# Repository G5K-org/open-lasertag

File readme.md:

<div align="center">

# Open Lasertag

**Infrarot-Lasertag zum Selberbauen – ESP32-S3 in der Waffe, passive Sensorweste, Spielserver in Python**

</div>

## Was ist das?

Ein komplettes Lasertag-System im Eigenbau für Spiele in einer großen Halle:

- **Waffe:** ein 3D-gedrucktes MP5-Gehäuse mit einer eigenen Platine. Darauf
  sitzt ein ESP32-S3, der alles steuert: IR-Schuss, Trefferauswertung,
  Lebens- und Munitionsanzeige, Mündungsfeuer, Vibration, Sound, Akku und WLAN.
- **Weste:** nur passive IR-Empfänger (TSOP34838) an Stirnband, Brust, Rücken
  und Schultern, per Kabel an der Waffe. Die Weste hat keine eigene Elektronik.
- **Server:** ein Python-Programm mit Live-Anzeige im Browser. Es zählt
  Punkte, führt Runden und gibt den Respawn frei.
- **Gateway (optional):** ein kleiner ESP32 am Server-PC. Über ihn erreichen
  die Waffen den Server per ESP-NOW, wenn das WLAN ausfällt.

Geschossen wird mit einer 940-nm-IR-LED hinter einer Linse, nicht mit einem
echten Laser. Die Spiellogik läuft lokal in der Waffe, damit Treffer sofort
Licht, Ton und Vibration auslösen. Das Netz meldet nur nach.

## Inhalt

- [Funktionen](#funktionen)
- [Systemüberblick](#systemüberblick)
- [Hardware](#hardware)
- [Gehäuse](#gehäuse)
- [Firmware](#firmware)
- [Server und Live-Anzeige](#server-und-live-anzeige)
- [Schnellstart](#schnellstart)
- [Projektstruktur](#projektstruktur)
- [Stand](#stand)
- [Planung im Detail](#planung-im-detail)
  1. [Grundentscheidungen](#1-grundentscheidungen)
  2. [Architektur](#2-architektur)
  3. [Sensorkabel zwischen Weste und Waffe](#3-sensorkabel-zwischen-weste-und-waffe)
  4. [IR-Protokoll und Trefferlogik](#4-ir-protokoll-und-trefferlogik)
  5. [Netzwerk](#5-netzwerk)
  6. [Anzeige und Feedback](#6-anzeige-und-feedback)
  7. [Risiken und Gegenmaßnahmen](#7-risiken-und-gegenmaßnahmen)
  8. [ESP32-Wahl](#8-esp32-wahl)
  9. [Vorgehen](#9-vorgehen)
  10. [Offene Punkte](#10-offene-punkte)

## Funktionen

| | |
|---|---|
| 🔫 **Schuss** | NEC-codiertes IR-Signal (Team + Spieler-ID), 38 kHz, jeder Schuss 2× gesendet; Ziel 30–50 m Reichweite |
| 🎯 **Treffer** | bis zu 6 Sensoren; Treffer zählt erst bei 2 gültigen Frames in 100 ms, danach 500 ms unverwundbar; Kopftreffer geben Bonuspunkte |
| 💡 **Anzeige** | WS2812-Kette an der Waffe: Lebensbalken grün → gelb → rot, Munition, Teamfarbe, Ringlicht als Mündungsfeuer; Anschlüsse für OLED (I²C) und Drehdrück-Geber |
| 📳 **Feedback** | Rückstoß- und Treffervibration, Soundeffekte über I²S-Verstärker, weißer Blitz bei Treffer, rotes Pulsieren als tot |
| 🔋 **Akku** | 1S-LiPo/18650 mit Schutzschaltung auf der Platine, Laden über USB-C, Spannungs- und Ladeanzeige; per USB auch ohne Akku lauffähig |
| 📡 **Netz** | WLAN mit eigenem Roaming zwischen Access Points, UDP mit HMAC-Signatur, Treffer werden bis zur Bestätigung wiederholt |
| 🛟 **ESP-NOW** | Fallback zum Server über ein Gateway, wenn das WLAN ausfällt; Trefferbestätigung direkt an die Waffe des Schützen (Ton + grüner Blitz) |
| 🖥️ **Server** | Runden mit Zeitlimit, Teamwertung, Respawn-Freigabe, Live-Anzeige und Bedienung im Browser, Latenzmessung pro Hallenzone |

## Systemüberblick

```mermaid
flowchart LR
    subgraph Weste["Weste (nur Sensoren)"]
        T1["TSOP 1<br>Stirn vorn"]
        T2["TSOP 2<br>Stirn hinten"]
        T3["TSOP 3<br>Brust"]
        T4["TSOP 4<br>Rücken"]
        T5["TSOP 5<br>Schultern"]
    end
    subgraph Waffe["Waffe (ESP32-S3)"]
        RX["IR-Empfang<br>RMT + GPIO"]
        GAME["Spiellogik<br>HP, Munition, Respawn"]
        TX["IR-LED<br>38 kHz"]
        FX["WS2812, Ringlicht,<br>Vibration, Sound"]
        NET["WLAN / UDP"]
    end
    SRV["Server (Python)<br>Punkte, Runden"]
    GW["Gateway<br>ESP32-C3"]
    WEB["Browser<br>Live-Anzeige"]
    W2["andere Waffe"]

    Weste -->|"Sensorkabel<br>GX16, 7 Adern"| RX
    RX --> GAME
    GAME --> TX
    GAME --> FX
    GAME <--> NET
    NET <-->|"WLAN: UDP + HMAC"| SRV
    NET <-.->|"Fallback: ESP-NOW"| GW
    GW <-->|USB| SRV
    NET -.->|"ESP-NOW: Treffer bestätigt"| W2
    SRV <-->|WebSocket| WEB
    TX -.->|IR-Schuss| G(("Gegner"))
```

## Hardware

Eine Platine für die ganze Waffe: 59,6 × 55 mm, 4 Lagen, nur SMD-Bauteile, von
Hand geroutet und für die Bestückung bei JLCPCB vorbereitet. Alle Peripherie
hängt an Steckern: Akku, IR-LED, Taster, Motoren, Lautsprecher, WS2812, ein Sensor an der Waffe und
das Sensorkabel der Weste. Ein- und ausgeschaltet wird mit dem Taster des Drehgebers (kurz drücken = ein,
2 s = aus; ausgeschaltet fließen ca. 55 µA). Geladen wird über USB-C mit 2 A.

| Oberseite | Unterseite |
|---|---|
|  |  |

**Auf der Platine:** ESP32-S3-WROOM-1 (16 MB Flash, 8 MB PSRAM; optional WROOM-1U mit externer Antenne), USB-C mit
ESD-Schutz zum Flashen und Laden, Lade- und 5-V-IC IP5306 (2 A Laden), Akkuschutz DW01A + FS8205A,
3,3-V-Regler, MOSFETs für IR-LED und Vibrationsmotor, Pegelwandler für
WS2812, I²S-Verstärker MAX98357A, microSD-Slot für Audio-Dateien (optional SPI-NAND-Flash 128 MB),
GX16-Buchse für das Sensorkabel der Weste (TSOP-Leitungen über 100 Ω).

Schaltplan, Layout, Fertigungsdaten und Design-Entscheidungen:
[kicad/waffe_elektronik/](kicad/waffe_elektronik/) · Pinbelegung:
[pinbelegung.md](pinbelegung.md)

## Gehäuse

Als Basis dient das Modell
[MP5 Toygun Cosplay](https://makerworld.com/de/models/427808-mp5-toygun-cosplay)
von **WIZZY** (MakerWorld). Es ist eine rein statische Requisite und wird für
Platine, Akku, Lautsprecher und Optik ausgehöhlt und angepasst. Vorne an der
Mündung sitzt ein WS2812-Ring als Mündungsfeuer.

Die Originaldateien liegen wegen der MakerWorld-Lizenz nicht im Repo; Download und
Ablage beschreibt [gehaeuse/mp5_toygun_stls/](gehaeuse/mp5_toygun_stls/).

Die Platine sitzt im Unterteil zwischen Magazinschacht und Griff; die senkrechte
USB-C-Buchse schließt bündig mit einer Mulde in der linken Seitenwand ab. Im Schalldämpfer sitzen IR-LED und
verstellbare Linse, vorn das Ringlicht; der 18650-Akku steckt im Magazin, das OLED sitzt
angewinkelt vorn oben am Schaft, der Drehgeber unten im Griff, der Abzug löst einen Mikroschalter aus.
Im Handschutz sitzt ein Lautsprecher Ø 40 mit Basskammer, vorn unter dem Korn der TSOP 6. Gehäusehälften
(6 × M3) und die beiden Hälften des vorderen Handschutzes mit Schalldämpfer (5 × M3) sind mit
Einschmelzmuttern verschraubt; die vorderen Hälften umschließen einen Zapfen am hinteren Handschutz
und sind dort mit je 2 × M3 befestigt (ohne Kleber, lösbar). Das Sensorkabel der Weste steckt unten vorn
am Schaft in einer GX16-7-Buchse (Stecker hängt hinter dem Griff leicht schräg nach hinten unten). Links über
dem Griff ist der Sicherungshebel ein beweglicher Nachladehebel (Wippe auf einen verdeckten Taster). Links oben
über dem ESP32-Modul sitzt eine RP-SMA-Buchse für eine externe Knick-Stabantenne (Variante WROOM-1U), die
senkrecht nach oben neben Kimme und Korn steht. Gehäuse, Zwischenring, Handschutz und Schaft sind
mit Stahlstegen und je zwei Zugankern M4 vorn und hinten verspannt, der Zwischenring ist beidseitig
zentriert. Alle Kabelwege sind geprüft:
[gehaeuse/mp5_umbau/](gehaeuse/mp5_umbau/README.md#kabelwege).
Umgebaute und neue Druckteile: [gehaeuse/mp5_umbau/](gehaeuse/mp5_umbau/). Alle Teile samt
Platine zusammengesetzt: [gehaeuse/baugruppe/](gehaeuse/baugruppe/) (GLB/3MF).

| Umgebaute Waffe | Innen (linke Hälfte, Schaft und Magazin ausgeblendet) |
|---|---|
|  |  |

| Schalldämpfer mit Ringlicht und Linsenhülse | OLED am Schaft |
|---|---|
|  |  |

**Externe Antenne:** RP-SMA-Buchse in der linken Seitenwand, innen Pigtail als Schlaufe zum U.FL des WROOM-1U.

| Außen | Innen (linke Hälfte und Antenne ausgeblendet) |
|---|---|
|  |  |

**Explosionszeichnung:** alle Druckteile, die Platine und die Antennenteile, entlang ihrer Montagerichtung auseinandergezogen.

| Von links vorn | Von rechts |
|---|---|
|  |  |

**Schnitt durch den Schalldämpfer:** Linsenhülse (gold) mit Linse Ø 20 im Innengewinde M24 × 1,5,
von vorn verstellbar; dahinter die IR-LED im Sitz (21 mm hinter der Linse), Kabel nach hinten;
vorn die Frontkappe mit Ringlicht, unten der Kabelkanal für das Ringlicht.

**Schnitt durch den Handschutz** (rechte Hälfte): Lautsprecher Ø 40 (rot) strahlt nach hinten in eine
Schallkammer mit Löchern in den Rillen, davor die geschlossene Basskammer (ca. 42 cm³); oben der
Kabelschacht als offene Nut an der Teilungsfläche, darüber das Korn; rechts (blau) der Zapfen des
hinteren Handschutzes, den die vorderen Hälften umschließen.

**Schnitt durch Gehäuse und Schaft:** GX16-7-Buchse für das Sensorkabel der Weste unten vorn am Schaft
(gold, Mutter in einer Sechskanttasche), Stecker 15° nach hinten unten; der Westenschacht läuft schräg nach
vorn in den Motorschacht und zur Platine (J2).

## Firmware

ESP-IDF v6.0, nur offizielle Espressif-Komponenten. WLAN und Netz laufen auf
Core 0, IR-Empfang und Spiellogik auf Core 1.

- **IR:** Senden über RMT mit 38-kHz-Träger. TSOP 1–4 laufen über die vier
  RMT-Empfangskanäle, weitere Sensoren über GPIO-Interrupts. Beide Wege gehen
  in denselben NEC-Decoder.
- **Feedback:** WS2812 über `led_strip`, Vibration per PWM, Soundeffekte
  werden synthetisch erzeugt (keine Sound-Dateien). Flash und microSD für
  Audio-Dateien sind auf der Platine vorgesehen, die Firmware nutzt sie noch nicht.
- **Netz:** kein Stromsparmodus, eigenes Roaming unter −75 dBm, Treffer
  werden gepuffert und wiederholt, bis der Server bestätigt.
- **ESP-NOW:** ohne WLAN nach 5 s Fallback über das [Gateway](gateway/);
  getroffene Waffen bestätigen dem Schützen den Treffer direkt.
- **Einstellungen:** Team, Spieler-ID, WLAN, Server und Spielregeln unter
  `idf.py menuconfig`. Team und ID kann auch der Server setzen.

Details: [firmware/](firmware/)

## Server und Live-Anzeige

Reines Python (Standardbibliothek, keine Installation). Der Server nimmt die
UDP-Pakete der Waffen an, wertet Treffer und Abschüsse aus, führt Runden mit
Zeitlimit und gibt den Respawn frei. Im Browser gibt es Teamwertung,
Spielerwerte (HP, Munition, K/D, Akku, Signal, Latenz), Abschussliste und die
Latenz pro Access Point. Ein Waffen-Simulator erlaubt Tests ohne Hardware.

Details: [server/](server/) · ESP-NOW-Gateway: [gateway/](gateway/)

## Schnellstart

**Firmware bauen und flashen** (Platine über USB-C anschließen):

```sh
. ~/esp/esp-idf-v6.0.3/export.sh
cd firmware
idf.py menuconfig          # "Lasertag Waffe": WLAN, Server-IP, Team, Spieler
idf.py -p /dev/ttyACM0 flash monitor
```

**Server starten:**

```sh
cd server
cp config.example.json config.json   # Schlüssel wie in der Firmware eintragen
python3 -m lasertag_server --config config.json
# Live-Anzeige: http://<server-ip>:8080/
```

**Ohne Hardware ausprobieren:**

```sh
cd server
python3 -m lasertag_server &
python3 sim_weapon.py --count 6
```

## Projektstruktur

```
├── firmware/              ESP-IDF-Projekt der Waffe
│   ├── main/              Module: IR, Spiellogik, LEDs, Sound, Netz, …
│   ├── test/              Host-Test des NEC-Decoders
│   └── tools/             kleiner UDP-Testserver
├── gateway/               ESP-NOW-Gateway (ESP32-C3) für den Server
├── server/                Spielserver in Python
│   ├── lasertag_server/   UDP, Spiellogik, Web/WebSocket, Oberfläche
│   ├── sim_weapon.py      Waffen-Simulator
│   └── tests/             Unit-Tests
├── kicad/waffe_elektronik/
│   ├── scripts/           Generatoren für Schaltplan (5 Seiten) und Platine, 3D-Modelle
│   ├── symbols/, footprints/, 3dmodels/   Projektbibliotheken
│   ├── renders/           Bilder von Platine und Schaltplan
│   └── fertigung/jlcpcb/  Gerber, BOM, CPL
├── gehaeuse/              MP5-Umbau: Druckteile, Baugruppe, Skripte (Basis-STL per Download)
├── docs/bilder/           Screenshots
├── pinbelegung.md         GPIO-Belegung des ESP32-S3
└── roadmap.md             Phasenplan
```

## Stand

| Teil | Stand |
|---|---|
| Schaltplan und Platine | fertig (Schaltplan auf fünf Seiten), ERC ohne Meldungen, DRC ohne Fehler, Bestellpaket für JLCPCB erstellt |
| Firmware | erste Fassung, auf einem ESP32-S3 geflasht und gestartet; Peripherie noch nicht getestet |
| Server | erste Fassung, mit simulierten Waffen getestet |
| ESP-NOW | Fallback Waffe ↔ Gateway ↔ Server mit zwei ESP32-S3 getestet (beide Richtungen, RTT ~22 ms); Trefferbestätigung Waffe zu Waffe noch ungetestet |
| Gehäuse | Umbau konstruiert (Druckteile, Baugruppe, Kabelwege geprüft), noch nicht gedruckt |
| Weste | Sensoren und Kabel geplant |

Nächste Schritte im [Phasenplan](roadmap.md).

## Lizenz

© 2026 Lucas Giesecke. Firmware, Server, Gateway, Schaltplan, Platine, Gehäuseumbau, Skripte und
Dokumentation stehen unter [CC BY-NC-SA 4.0](LICENSE)
(Namensnennung – nicht kommerziell – Weitergabe unter gleichen Bedingungen):

- **erlaubt:** nutzen, nachbauen, verändern, weiterentwickeln und weitergeben, mit Namensnennung
  und Link auf dieses Projekt; Abwandlungen unter derselben Lizenz
- **nicht erlaubt ohne meine Einwilligung:** kommerzielle Nutzung, z. B. Verkauf von Platinen,
  Bausätzen, Waffen oder Druckteilen, bezahlte Veranstaltungen mit den Geräten, Einbau in
  kommerzielle Produkte. Anfragen bitte als Issue oder direkt an mich

Ausgenommen sind Teile Dritter, für sie gelten ihre eigenen Lizenzen:

| Teil | Quelle | Lizenz |
|---|---|---|
| Gehäusebasis (Originaldateien nicht im Repo, Download siehe `gehaeuse/mp5_toygun_stls/`) und die daraus abgeleiteten Teile in `gehaeuse/mp5_umbau/`, `gehaeuse/baugruppe/` | [MP5 Toygun Cosplay](https://makerworld.com/de/models/427808-mp5-toygun-cosplay) von WIZZY | MakerWorld Standard-Digitaldatei-Lizenz |
| `kicad/waffe_elektronik/fonts/` | Orbitron, Share Tech Mono | SIL Open Font License 1.1 |

---

# Planung im Detail

Stand der Planung: 08.10.2026

## 1. Grundentscheidungen

| Thema | Entscheidung |
|---|---|
| Strahl | IR-LED 940 nm + Linse, kein echter Laser |
| Empfänger | TSOP34838 (Tageslichtfilter) |
| Aufteilung | Ein ESP32-S3 in der Waffe, Weste trägt nur noch passive TSOP-Sensoren |
| Verbindung Weste–Waffe | reines Sensorkabel (3,3 V + GND + je 1 Ader pro TSOP) |
| Netz | WLAN + UDP zu einem Server |
| Spiellogik | lokal in der Waffe (HP, Vibration, LEDs, Sound), Netz meldet nur nach |
| ESP-NOW | Fallback zum Server über ein Gateway und Trefferbestätigung Waffe zu Waffe, WLAN bleibt der Hauptweg |
| Firmware-Framework | ESP-IDF, kein Arduino – nur offizielle Espressif-Komponenten (RMT, I²S, led_strip, esp_wifi) |

---

## 2. Architektur

Übersichtsdiagramm siehe [Systemüberblick](#systemüberblick).

### Waffe (ESP32-S3, zentrale Elektronik – einziger Chip)
- IR-LED (TSAL6100 o. ä.) über N-MOSFET (AO3400 / IRLZ44N), Gate 100 Ω, Pulldown 100 kΩ
- 2 × 22 µF Keramik (C7, C19) als Puffer zwischen Akku und GND
- Abzug und Nachladen (Mikrotaster, RC-Entprellung 10 kΩ + 100 nF)
- Munitionszähler: WS2812-Kette, dazu kleines OLED (I²C) und Drehdrück-Geber, je an eigenem Stecker
- Ein Vibrationsmotor für Rückstoß und Treffer (MOSFET, Freilaufdiode, PWM)
- 4–5× TSOP34838-Signale von der Weste, lokale RMT-Auswertung
- Zusätzlicher TSOP34838 an der Waffe (Stecker J6 zusammen mit der IR-LED, GPIO16, Filter
  100 Ω + 4,7 µF am Sensor, nicht über das Sensorkabel)
- WS2812(B)-Streifen, echte 5-V-Variante (HP/Treffer/Team-Farbe), an der Waffe
  montiert. 5 V für den Strip aus dem IP5306 (Boost vom 1S-LiPo), plus Pegelwandler (z. B.
  ein N-MOSFET in Gateschaltung) zwischen 3,3-V-GPIO und Datenleitung.
- I²S-Verstärker (MAX98357A) + Lautsprecher, nutzt dieselben 5 V wie der
  WS2812-Strip
- SPI-NAND-Flash ZD35Q1GC (128 MB) für Audio-Dateien, optional (Standard: nur microSD), an IO7/IO15/IO3/IO46
- microSD-Slot (Push-Pull, TF-018) am selben SPI-Bus, /CS an IO48; Karte nur bei geöffnetem Gehäuse
  erreichbar
- 1S-LiPo oder 18650, Akkuschutz (DW01A + FS8205A) auf der Platine, Akkuspannung per ADC, im Waffengehäuse
- ESP32-S3-WROOM-1 direkt auf der Platine, eigene USB-C-Buchse am nativen USB
  (IO19/IO20) zum Flashen, Debuggen und Laden – Auto-Flash über den
  eingebauten USB-Serial-JTAG, BOOT- und RESET-Taster als Rückfallebene
- Laden über USB-C mit 2 A: IP5306 (Schaltlader + 5-V-Boost, eigener I²C-Bus, siehe
  [pinbelegung.md](pinbelegung.md)); USB speist über eine Schottky-Diode auch die 5-V-Schiene, damit Flashen
  ohne Akku geht
- WLAN auf Core 0, IR-Auswertung auf Core 1

### Weste (nur Sensoren, keine eigene Elektronik)
- 4–5 TSOP34838: Stirnband vorn/hinten, Brust, Rücken, Schultern
- Je Sensor 100 Ω + 4,7 µF direkt am VCC-Pin, am Sensor selbst
- Kein Chip, keine Platine – nur Sensoren und das Sensorkabel zur Waffe

---

## 3. Sensorkabel zwischen Weste und Waffe

Die Weste hat keinen eigenen Chip – nur TSOP-Sensoren, reine Signalleitungen,
kein Protokoll.

| Ader | Signal |
|---|---|
| 1 | 3,3 V |
| 2 | GND |
| 3 | TSOP 1 – Stirnband vorn |
| 4 | TSOP 2 – Stirnband hinten |
| 5 | TSOP 3 – Brust |
| 6 | TSOP 4 – Rücken |
| 7 | TSOP 5 – Schultern (optional) |

- 7 Adern (bei 5 Sensoren): GX16-7-Aviation-Steckverbinder mit Schraubverriegelung.
  Buchse unten vorn am Schaft, im Gehäuse Litzen zu J2 (JST-SH 7), siehe
  [Weste im Gehäuse](gehaeuse/mp5_umbau/README.md#einbau).
- Je TSOP 100 Ω + 4,7 µF direkt am Sensor, nicht erst an der Waffe; auf der Platine
  liegt jede TSOP-Leitung über 100 Ω in Reihe (Schutz der GPIOs).
- Kabel kurz halten, geschirmt.
- Reine GPIO/RMT-Eingänge, von derselben Firmware ausgewertet, die auch sendet.

---

## 4. IR-Protokoll und Trefferlogik

- NEC-Timing über den offiziellen ESP-IDF RMT-Treiber (`driver/rmt_tx.h` /
  `rmt_rx.h`) encodieren/decodieren; Adresse = Team, Command = Spieler-ID
- Optional später eigenes kürzeres Protokoll (38 kHz, 2 Bit Team, 6 Bit ID,
  Parität)
- Treffer nur zählen bei: Team ungleich eigenem Team (Friendly Fire als
  Schalter), 2 gültige Pakete innerhalb 100 ms, Wiederholcodes ignorieren
- 500 ms Unverwundbarkeit nach Treffer
- Während des Sendens Empfang pausieren, eigene ID ignorieren
- FreeRTOS-Tasks mit `vTaskDelay()`/`esp_timer_get_time()` statt Busy-Loops
- Keine Zonenerkennung (Kopf/Arm/Bein); Kopf-Bonus über Regeln

### Reichweite (IR)
- Linse Ø 25 mm, f ≈ 40–50 mm, LED knapp hinter dem Brennpunkt
- Spitzenstrom 150–300 mA gepulst, Tastgrad 25–33 %
- Eine IR-LED (TSAL6100) mit Vorwiderstand 2 × 22 Ω parallel (11 Ω), Kabel über J6 zusammen mit TSOP 6
- Schuss 2× kurz hintereinander senden
- Ziel: 30–50 m frei

---

## 5. Netzwerk

- Eigene SSID nur 2,4 GHz, eigenes VLAN, Band-Steering aus
- Feste Kanäle (1/6/11), Auto-Optimize während des Spiels aus
- Minimum RSSI ca. -75 dBm, DTIM 1, 802.11r für diese SSID eher aus
- Server und möglichst viele APs per Kabel anbinden
- Waffe: `esp_wifi_set_ps(WIFI_PS_NONE)`, statische IP, keine Scans im Spiel
- UDP-Pakete mit Laufnummer, Treffer 2× senden, bei Aussetzern puffern und
  nachsenden
- Pakete mit Shared-Secret/HMAC absichern
- Eigene Roaming-Logik: RSSI alle 1–2 s prüfen, unter ca. -75 dBm gezielt
  wechseln
- Latenzmessung: Zeitstempel + Echo vom Server, RTT pro Hallenzone loggen
- Erwartung: 3–15 ms, Ausreißer bis 200 ms bei Roaming
- ESP-NOW als Rettungsanker: ohne WLAN Fallback über ein Gateway-ESP32 am
  Server (fester Kanal), dazu Trefferbestätigung direkt an den Schützen. ESP-NOW
  funkt auf dem aktuellen WLAN-Kanal, Waffen hören sich also nur auf gleichem
  Kanal

### Server
- UDP-Listener als eigener asyncio-`DatagramProtocol`, Deduplizierung über
  (Spieler-ID, Laufnummer)
- Teams, Punkte, Runden, Respawn-Freigabe
- Live-Anzeige als Webseite (WebSocket)

---

## 6. Anzeige und Feedback

Komplett an der Waffe montiert (WS2812-Streifen, Vibration, Lautsprecher).

- Lebensanzeige: WS2812-Streifen an der Waffe über das offizielle
  ESP-IDF-`led_strip`-Component, 1 LED = 10 % HP, grün → gelb → rot, unter
  20 % blinken
- Treffer: Vibration 200–300 ms, weißer Blitz 150 ms, Treffer-Ton, Richtung
  über Sensor-Segment
- Tod: rot pulsierend bis Respawn, langes Vibrationsmuster
- Team: Lichtband an der Waffe in Teamfarbe
- Mündungsfeuer: WS2812-Ringlicht vorne an der MP5, als letztes Glied der
  WS2812-Kette über denselben LED-Stecker (kein eigener Pin), kurzer warmer
  Blitz bei jedem Schuss, Helligkeit wegen Stromspitze an der 5-V-Versorgung begrenzt
- Lokale Anzeige zuerst, Netzmeldung danach
- Helligkeit per Skalierungsfaktor in der `led_strip`-Pixel-Berechnung
  begrenzen, Diffusor über den LEDs

---

## 7. Risiken und Gegenmaßnahmen

| Risiko | Maßnahme |
|---|---|
| WLAN stört IR-Empfang | S3 mit Core-Trennung, RC-Filter am TSOP, ggf. RMT-Empfang |
| Reflexionen an Regalen/Folie | 2 gültige Pakete, früh an Gangkreuzungen testen |
| PWM-gedimmte Hallenbeleuchtung stört/blendet TSOP | früh unter realer Beleuchtung testen, ggf. Dimmfrequenz der Lampen prüfen |
| Spannungseinbruch beim IR-Puls | Elko am MOSFET, ausreichend dicke Adern |
| Kabelbruch / Sensorkabel löst sich | Zugentlastung, GX12/GX16-Steckverbinder mit Schraubverriegelung statt loser Stecker |
| TSOP-Signale über längeres Kabel anfälliger für Störungen | kurz halten, geschirmt/verdrillt, RC-Filter direkt am Sensor |
| Team-/HP-Anzeige an der Waffe schlechter sichtbar als am Körper | im Praxistest prüfen, ggf. Sensorkabel später um WS2812-Datenader erweitern |
| Gewicht/Balance der Waffe (Akku, Lautsprecher, LED jetzt alle dort) | früh mit Gesamtgewicht prototypisch testen, ggf. Akku in den Griff/Schaft verlegen |
| WS2812-Datensignal bei 3,3 V unzuverlässig | Pegelwandler (N-MOSFET in Gateschaltung) |
| Augen | IR-LED-Datenblatt und IEC 62471 prüfen, nicht aus der Nähe in die Optik schauen |
| LiPo in der Halle | Schutzschaltung, geschütztes Laden (LiPo-Beutel), nie unbeaufsichtigt |
| Unfallgefahr | nur gehen, Schutzschuhe, Staplerbereiche sperren |
| Organisation | Chef, Versicherung, ggf. Betriebsrat vorher klären |

---

## 8. ESP32-Wahl

| Chip | Status |
|---|---|
| ESP32-S3 | Einziger Chip, in der Waffe |
| ESP32-C3 SuperMini (vorhanden) | nicht mehr im Einsatz – als Ersatzteil aufheben |
| ESP32-C6 | entfällt |
| ESP32 (WROOM) | entfällt |

Befestigung: Platine mit Buchsenleisten und M3-Abstandshaltern oder gedruckte
PETG-Halterung mit Schnappnasen, Antenne frei halten (≥ 10–15 mm Abstand zu
Akku und Metall), USB-Zugang einplanen.

---

## 9. Vorgehen

1. Waffe mit angeschlossenen TSOP-Sensoren auf dem Tisch, nur IR: Reichweite und Fehltreffer messen
2. IR-Stresstest (1000 Schüsse bei laufendem WLAN und LED-Animation, Ziel ≥ 99 %)
3. Sensorkabel Weste → Waffe verlegen und auswerten
4. WLAN/UDP zum Server, RTT pro Hallenzone loggen
5. Spiellogik (Teams, HP, Respawn, Runden) auf dem Server
6. Optik- und Schaltungsoptimierung nach Messwerten
7. Danach weitere Westen, Sound, Extras

---

## 10. Offene Punkte

- Waffe-Code: erste Fassung in [firmware/](firmware/) (ESP-IDF v6.0, auf ESP32-S3 geflasht, Peripherie noch nicht getestet)
- Server: erste Fassung in [server/](server/) (Python, nur Standardbibliothek, mit Waffen-Simulator getestet)
- Gehäuse/3D-Druck-Maße, inkl. Platz für Akku/Lautsprecher/LED in der Waffe –
  als Basis ausgewählt: [MP5 Toygun Cosplay](https://makerworld.com/de/models/427808-mp5-toygun-cosplay)
  (Quellenangabe und Download in [gehaeuse/mp5_toygun_stls/](gehaeuse/mp5_toygun_stls/)),
  Umbau in [gehaeuse/mp5_umbau/](gehaeuse/mp5_umbau/); offen: Nachlade-Taster,
  WS2812-Lebensbalken/Munitionsanzeige
- Akku-/Laufzeitbudget (WLAN + WS2812 + Sound + IR-Pulse) für Eventplanung
- OTA-Update-Mechanismus für die Waffe bei mehreren Sets
- CI-Build für die Firmware
- Server (Python) folgt eigener Umsetzung, ohne externe Basis – ESP-IDF-Vorgabe gilt nur für die Firmware
- Gewichtsverteilung der Waffe mit Gesamt-BOM früh real nachbauen/wiegen

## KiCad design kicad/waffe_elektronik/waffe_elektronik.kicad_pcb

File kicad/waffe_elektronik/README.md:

# waffe_elektronik – KiCad-Projekt

Schaltplan und Platine für die zentrale Elektronik der Waffe (einziger
ESP32-S3-Chip), passend zu [../../pinbelegung.md](../../pinbelegung.md) und
[../../readme.md](../../readme.md). KiCad 10, ERC 0 Fehler und 0 Warnungen, DRC 0 Fehler.

## Öffnen

`waffe_elektronik.kicad_pro` in KiCad öffnen, dann Schaltplan- bzw.
Platinen-Editor starten. Die Bibliotheken sind über die mitgelieferte projekteigene
`sym-lib-table` eingebunden (nur Standard-KiCad-Bibliotheken, z. B. `Device`,
`Diode`, `Transistor_FET`, `74xx`, `power`).

## Aufbau

Hierarchischer Schaltplan: ein Übersichtsblatt (`waffe_elektronik.kicad_sch`, A4) mit fünf A3-Unterblättern,
jedes in gestrichelt umrahmte Funktionsblöcke gegliedert:

| Seite | Datei | Blöcke |
|---|---|---|
| 2 [Stromversorgung](renders/schaltplan_1_stromversorgung.png) | `stromversorgung.kicad_sch` | Laden + 5 V (IP5306) + LDO, Akku-Messung, Akkuschutz + USB-Versorgung, Akku + Ein/Aus |
| 3 [ESP32-S3 und USB](renders/schaltplan_2_mcu_usb.png) | `mcu_usb.kicad_sch` | ESP32-S3-WROOM-1, USB-C |
| 4 [Bedienung und Aktoren](renders/schaltplan_3_bedienung_aktoren.png) | `bedienung_aktoren.kicad_sch` | IR-Sender, Abzug/Nachladen, WS2812, Vibration, OLED + Drehgeber |
| 5 [Audio und Speicher](renders/schaltplan_4_audio_speicher.png) | `audio_speicher.kicad_sch` | Sound (I²S), Flash, microSD |
| 6 [Sensoren](renders/schaltplan_5_sensoren.png) | `sensoren.kicad_sch` | Weste, TSOP 6, Serienwiderstände im Sensorkabel |

- Innerhalb eines Blocks ist alles mit echten Leitungen verdrahtet; Bauteile
  liegen auf dem Raster, Versorgung zeigt nach oben, Masse nach unten.
- Zwischen den Blöcken und Seiten laufen Signale über globale Labels an kurzen
  Stichleitungen (z. B. `IR_GATE`, `TSOP1_OUT`) statt über lange Leitungen.
- Versorgungsnetze (`GND`, `3V3_MCU`, `5V_PERIPH`, `BAT_P`, `VBUS_NATIVE`)
  hängen an KiCad-Power-Symbolen.
- Unbenutzte Pins sind markiert: freie GPIOs mit No-Connect-Kreuz.
- Bauteile in der Waffe (IR-LED, TSOP 6, Abzugs- und Nachladeschalter) und auf der Weste stehen im Schaltplan
  ohne Footprint jenseits ihres Steckers.

Schaltplan ([kiutils][1]) und Platine (pcbnew) werden per Python erzeugt und
mit `kicad-cli` geprüft; die Generator-Skripte liegen in [`scripts/`](scripts/).
Die Footprints der senkrechten USB-C-Buchse (J3) und des microSD-Slots (J7, Pads nach LCSC/EasyEDA) liegen in der Projektbibliothek
[`footprints/lasertag.pretty`](footprints/lasertag.pretty) (`fp-lib-table`), ihr 3D-Modell
erzeugt `freecadcmd scripts/gen_3d_usb_c_vertical.py`.
3D-Modelle der JST-PH-SMD-Stecker (BT1, SP1, J1) und des WSON-8 8×6 (U14) liegen in [`3dmodels/`](3dmodels/)
(STEP + WRL, erzeugt mit `freecadcmd scripts/gen_3d_jst_ph_sm4.py` bzw. `scripts/gen_3d_wson8_8x6.py`),
das Modell des microSD-Slots (J7) stammt aus der LCSC/EasyEDA-Bibliothek (C961679).

[1]: https://github.com/mvnmgrx/kiutils

## Bauteile

Die Symbole stammen aus den KiCad-Standardbibliotheken; FS8205A, IP5306 sowie Kopien von `W25Q32JVZP`
(/WP, /HOLD passiv) und `MAX98357A` (Pad = Masse) liegen in der Projektbibliothek
[`symbols/lasertag.kicad_sym`](symbols/lasertag.kicad_sym), die `build_clean.py` aus dem erzeugten Schaltplan
schreibt. Verwendet u. a.
`ESP32-S3-WROOM-1` (`U4`), `USB_C_Receptacle_USB2.0_16P` (`J3`),
`USBLC6-2SC6`, `AMS1117-3.3`, `TSOP348xx`,
`MAX98357A`, `AO3400A`, `SS14` (Pinbild für B5819W), `W25Q32JVZP` (Pinbild für U14), `Micro_SD_Card_Det1`,
`DW01A`, `D_Schottky`. Alle Footprints sind
SMD, J3 aus der Projektbibliothek; Bauteile außerhalb der Platine (Akku, IR-LED, TSOP 6, Taster, Motoren,
Lautsprecher, WS2812, Weste) sind über JST-SH/-PH-Stecker angeschlossen.

## Design-Entscheidungen im Schaltplan

- **ESP32-S3-WROOM-1 direkt auf der Platine** (kein DevKit):
  - 3V3 mit 100 nF + 10 µF direkt am Modul
  - EN mit 10 kΩ Pull-up und 1 µF (Power-on-Reset), dazu RESET-Taster
  - BOOT-Taster an IO0
- **USB-C (`J3`) am nativen USB des S3** (IO19/IO20 = USB_D−/USB_D+):
  - senkrechte Buchse hanxia HX-TYPE-C 16P 180 LT H10.5 (LCSC C49261570), 10,5 mm hoch;
    Stecker kommt von der Bestückungsseite, die Buchse reicht in der Waffe durch die linke Seitenwand
    und schließt bündig mit einer flachen Mulde außen ab
  - Flashen und serielle Konsole über den eingebauten USB-Serial-JTAG –
    esptool setzt das Modul automatisch in den Download-Modus, ohne
    USB-UART-Chip
  - Hängt die Firmware oder belegt sie die USB-Pins: BOOT halten und RESET
    drücken, dann lässt sich trotzdem flashen
  - CC1/CC2 je 5,1 kΩ nach GND, damit USB-C-Netzteile VBUS einschalten
  - ESD-Schutz USBLC6-2SC6 in D−/D+ und VBUS
- **Laden und 5 V (`U1`, IP5306-I2C, LCSC C488349):** ein Schaltregler mit einer Spule (`L1` 1 µH,
  MWSA0503S-1R0MT) lädt den Akku aus USB-C (bis 2,1 A, Ladestrom per I²C) und erzeugt aus dem Akku
  `5V_PERIPH`; mit USB kommen die 5 V direkt aus VBUS (Powerpath). VIN 10 µF (`C4`) + Dämpfung 2 Ω/10 µF
  (`R1`/`C29`, an der VBUS-Leitung bei der USB-Buchse), VOUT 22 µF + 10 µF (`C20`, `C30`), BAT-Messeingang über 1 Ω/22 µF (`R2`/`C5`), Akku 22 µF (`C19`).
  Eigener I²C-Bus an IO18 (SCL) / IO9 (SDA), je 4,7 kΩ (`R40`/`R38`) auf 3V3
- **Lastschalter hinter VOUT (`U16`, TPS22810DBV, LCSC C205990):** der IP5306 lässt im Standby eine Restspannung
  (0,8–2,8 V) an VOUT stehen; `U16` trennt `5V_PERIPH` davon ab. EN hängt an IRQ des IP5306 (Pin 4, high solange
  er arbeitet, hochohmig im Standby) mit 100 kΩ nach GND (`R42`); CT 10 nF (`C33`) → ca. 1 ms Anstieg, begrenzt den
  Einschaltstrom in die 5-V-Kondensatoren. Notlösung, falls IRQ sich anders verhält: Pin 1 und 6 von `U16` brücken
- **Ein/Aus:** der Taster des Drehgebers (J5 Pin 2, `PWR_KEY`) geht über `D6` (BAT54CW, Anode 1; Doppel-Schottky mit kleinem Sperrstrom, sonst zieht der Leckstrom in den stromlosen
  IO21 KEY nach unten) und 10 kΩ
  (`R24`) an KEY des IP5306 und über die zweite Anode an IO21. Ein: kurz drücken; aus: 2 s drücken oder per
  I²C (Register siehe [pinbelegung.md](../../pinbelegung.md)); IO21 liest den Taster über die zweite Anode. Ausgeschaltet ziehen Akkuschutz und IP5306
  zusammen ca. 55 µA
- **Power-Tree:** Akku → Akkuschutz → IP5306 (`U1`) → Lastschalter (`U16`) → `5V_PERIPH` (speist WS2812, MAX98357A) →
  AMS1117-3.3 (`U2`) → `3V3_MCU` (ESP32-S3 und Pull-ups); IR-LED und Akku-Messung (1 MΩ/1 MΩ) direkt am Akku
- **Akkuschutz:** DW01A (`U15`, LCSC C351410) + FS8205A (`Q3`, C2830320) im Minuspfad des Akkus
  (`BAT_N` → `GND`): trennt bei ca. 4,3 V, 2,4 V und Überstrom (ca. 3 A); VCC über 100 Ω (`R28`) + 100 nF
  (`C27`), CS über 1 kΩ (`R29`)
- **USB ohne Akku:** Schottky B5819W (`D4`) von `VBUS_NATIVE` auf `5V_PERIPH`
- **IR-LED:** Vorwiderstand 2 × 22 Ω parallel (`R7`, `R8`, 1206, ca. 240 mA Spitze bei vollem Akku), Puffer
  `C7` + `C19` (je 22 µF) am Akku; LED und TSOP 6 teilen sich den Stecker `J6` (1 LED-Anode, 2 LED-Kathode,
  3 GND, 4 3V3, 5 TSOP-Ausgang; LED-Adern im Kabel verdrillt, GND zwischen LED und Sensor)
- **3V3 in die Kabel über 10 Ω:** Weste (`R35`, Netz `3V3_WESTE`) und J6 (`R36`, `3V3_J6`); ein Kurzschluss im Kabel
  oder beim Stecken des GX16 zieht `3V3_MCU` nicht herunter
- **5-V-Puffer:** 22 µF 0805 (Basic): `C20` am IP5306 (dazu `C30` 10 µF 0603, kein Platz für 0805; 22 µF in 0603 gibt es als Basic nur mit 6,3 V), `C1`/`C31` am 5-V-Stamm, `C10`/`C32` am WS2812-Stecker
- **Abzug und Nachladen** über einen gemeinsamen Stecker `J8` (1 Abzug, 2 GND, 3 Nachladen)
- **Sensorkabel:** TSOP 1–5 je über 100 Ω (`R30`–`R34`) an J2
- **TSOPs:** je eigener 100 Ω/4,7 µF-Tiefpass direkt am Sensor (auf der
  Weste).
- **WS2812:** Pegelwandler 3,3→5 V mit einem N-MOSFET in Gateschaltung (`Q4` 2N7002 mit kleiner Ausgangskapazität,
  Gate an 3V3, Source am GPIO, Drain mit 1 kΩ `R25` auf 5 V, nicht invertierend) plus
  330 Ω-Vorwiderstand; die Munitionsanzeige hängt als weitere WS2812-Pixel am
  physischen DOUT-Pin des HP-Streifens (Daisy-Chain), am Ende der Kette sitzt
  das Ringlicht für das Mündungsfeuer vorne an der Waffe.
- **Flash für Audio-Dateien (`U14`, optional, Standard ohne):** SPI-NAND Zetta ZD35Q1GC-IB, 1 Gbit (128 MB), WSON-8 8×6,
  LCSC C2928927 (pin- und gehäusegleich: GD5F1GQ5UE, W25N01GV), ESP-IDF-Komponente `espressif/spi_nand_flash`; SPI2 über die GPIO-Matrix
  (IO7 /CS, IO15 MISO, IO3 MOSI, IO46 CLK), /CS mit 10 kΩ (`R27`) auf 3V3, /WP und /HOLD fest
  auf 3V3, 100 nF (`C25`) an VCC, EP auf GND
- **microSD-Slot (`J7`):** XKB TF-018, Push-Pull, LCSC C961679, im SPI-Modus am Flash-Bus
  (`SPI_CLK`/`SPI_MOSI`/`SPI_MISO`), /CS an IO48; Pull-ups an /CS und DAT0 intern im ESP32, DAT1/DAT2
  gemeinsam über 10 kΩ (`R37`), Kartenerkennung offen, 100 nF (`C26`)
- **PWR_FLAG-Symbole** (`#FLG*`) markieren Netze, die ERC sonst als "nicht
  getrieben" anmahnen würde (5 V, VBUS, Akku).

## Platine

| Oben | Unten |
|---|---|
|  |  |

- **59,6 × 55 mm** (Grundfläche 59,6 × 46 mm; oben links eine 18,6 × 9 mm große Lasche für Akkuschutz und Ein/Aus-Diode,
  rechts bei y 18,5–26,5 eine Aussparung für das Motorkabel), 1,6 mm, 4 Lagen, nur SMD, Bestückung nur oben
- **Lagen:**
  - F.Cu: Bauteile, kurze Signale, GND-Fläche
  - In1.Cu: durchgehende GND-Fläche ohne Leiterbahnen
  - In2.Cu: Versorgung (`5V_PERIPH`, `3V3_MCU`, `VBUS_NATIVE` zum IP5306, `BAT_P` zum DW01A) als Leiterbahnen + GND-Fläche
  - B.Cu: lange Signale (Abzug, Nachladen, IR, WS2812, IO0, TSOP, Bedienteil, Ein/Aus, I²C zum IP5306, Flash,
    microSD, VBUS) + GND-Fläche, Projekt-URL
- **ESP32-S3-Modul:** Antenne ragt über die Oberkante hinaus; jedes GND-Pad
  mit eigenem Via nach In1, GND-Stitching-Vias im Raster
- **Befestigung:** 2 × M2-Loch (2,2 mm, nicht durchkontaktiert) für Linsenkopfschrauben
  ISO 7380 (Kopf ≤ 3,5 mm), diagonal: neben dem Spannungsregler und unten zwischen USB-C und
  microSD-Slot; Ø 3,7 mm kupferfrei auf allen Lagen
- **Flash (U14):** unter dem Modul zwischen C1 und Vibrationstreiber; die vier SPI-Leitungen laufen auf
  B.Cu links an BOOT vorbei, /CS und MISO links in U14, MOSI und CLK unter U14 durch zu Vias rechts
  neben Pin 5/6; 3V3 für C25/R27/WP über einen In2-Abzweig der rechten 3V3-Leitung
- **microSD (J7):** unten rechts; Kontakte und Öffnung an der Unterkante (die Karte wird auf der Kontaktseite
  eingesteckt) und ragt ~7,6 mm in die Kabeltasche unter der Platine. Alle Leitungen laufen auf F.Cu unter dem
  Slot nach oben: MOSI, MISO und /CS über Vias bei y 39,2, CLK wechselt über dem Slot auf F.Cu, VDD gerade in
  C26 (100 nF), daneben C28 (10 µF) gegen den Einschaltstrom der Karte, DAT1/DAT2 über In2 unter dem Slot verbunden
- **Antenne:** Standard ist das ESP32-S3-WROOM-1 mit Leiterplattenantenne über der Oberkante. Optional passt
  das ESP32-S3-WROOM-1U-N16R8 (LCSC C3013946) ohne Änderung auf denselben Footprint (gleiche Pads, Modul
  6,3 mm kürzer, endet an der Oberkante); dazu Pigtail U.FL auf RP-SMA-Einbaubuchse (TE/Linx CSI-RGFB-100-UFFR)
  in der linken Seitenwand über dem Modul und Knick-Stabantenne außen (TE/Linx ANT-2.4-CW-HWR-RPS), siehe
  [Gehäuse](../../gehaeuse/mp5_umbau/README.md#einbau). 3D-Modell des 1U für die Baugruppe:
  `scripts/gen_3d_wroom1u.py`. JLCPCB-Dateien dafür:
  `waffe_elektronik_bom_externe_antenne.csv` und `waffe_elektronik_cpl_externe_antenne.csv` (Modulmitte 3,15 mm
  versetzt), Mouser: [`option_externe_antenne_10_waffen.csv`](fertigung/mouser/option_externe_antenne_10_waffen.csv)
- **Bedienung:** J4 OLED (JST-SH 4, Qwiic: GND/3V3/SDA/SCL) und J5 Drehgeber (JST-SH 4:
  GND/Taster/B/A) übereinander im rechten Streifen; I²C-Pull-ups auf dem OLED-Modul
- **Stecker nach Kabelweg in der Waffe:** jede Öffnung zeigt in die Zone am Platinenrand, aus der der
  Kabelschacht des Bauteils abgeht
  - links (vorn, Hauptschacht zum Lauf, Abzweig Magazin): Akku (BT1), IR-LED + TSOP 6 (J6),
    WS2812 (J1), Lautsprecher (SP1)
  - unten (Kanal zur Abzugsschalter-Tasche): Abzug + Nachladen (J8), Entprellung R9/C8 und
    R10/C9 direkt darüber; microSD-Karte (J7) rechts davon, die Abzugskabel liegen über ihr
  - rechts (hinten, Motorschacht): Vibrationsmotor (M1), Sensorkabel Weste (J2)
  - rechts oben: OLED (J4), Drehgeber (J5)
  - USB-C (J3) senkrecht unten rechts der Abzugsstecker, CC1/CC2-Widerstände R23/R22 direkt
    darüber/darunter; RESET-Taster auf dem EN-Weg oben links
- **Regeln (`.kicad_pro`):** min. 0,15 mm Leiterbahn/Abstand, Vias 0,5/0,3 mm
  (USB-Kreuzung 0,4/0,2 mm), Netzklassen Default 0,2 mm, Power 0,5 mm,
  3V3 0,6 mm, USB 0,2/0,2 mm (Paar)
- **Leiterbahnen so kurz wie möglich** auf allen Lagen: lange Wege als ein 45°-Abschnitt
  statt L-Form; parallele Bündel bleiben parallel und kreuzungsfrei
- **USB-Paar gleich lang:** D+ mit Mäander zwischen Modul und USBLC6 und zwischen USBLC6
  und Buchse; an der Buchse D+ über ein Via in der Buchsenmitte (A6–B6-Diagonale), D− über eine
  B.Cu-Brücke A7–B7 mit Abgriff in der Längenmitte; beide Steckrichtungen gleich lang
  (Modul–USBLC6 0,000 mm, USBLC6–Buchse ≤ 0,01 mm, je 2 Vias); VBUS A4/B9 und A9/B4 je über ein
  Via im Reihenspalt, links über B.Cu, rechts über In2 zum USBLC6
- **Beschriftung oben** (F.SilkS), alle Labels waagerecht und einheitlich 0,8 mm hoch,
  direkt am jeweiligen Stecker/Taster, frei von Pads, Vias und Bauteilkörpern; LED/TSOP unter J6, WS2812 neben und LAUTSPR. unter ihrem
  Stecker, TASTER rechts neben J8; Pin 1 von J2
  mit „1“ markiert; Bauteilbezeichner nur auf F.Fab
- **Leiterbahnen nur in 0°/45°/90°**, jeder Knick max. 45°, Abzweige laufen
  unter 45° ein; Teardrops an allen Pads und Vias (außer GND-Stichen in der
  GND-Fläche)
- **Hohe Ströme:** 5 V vom IP5306 über `U16` und zwei Vias in den In2-Stamm (1,2 mm, Abzweig zu WS2812/C10 1,0 mm); Akku-Minus
  BT1 → Akkuschutz 1,2 mm auf B.Cu mit je drei Vias
- **Routing von Hand**, kein Autorouter: IP5306-Schaltknoten gerade und breit zur Spule, Akku → Spule 1,2 mm,
  3V3 von der LDO-Kühlfläche über 10 µF + 100 nF direkt an Modul-Pin 2,
  USB-Paar 45° geführt, D+/D− an der Buchse über eine Via-Kreuzung
- Fertigungsdaten: JLCPCB-4-Lagen-Standardstackup (USB-Impedanz beim
  Fertiger prüfen)

## Fertigung (JLCPCB)

[`fertigung/jlcpcb/`](fertigung/jlcpcb/): `waffe_elektronik_gerber.zip` (Gerber + Bohrdaten),
`waffe_elektronik_bom.csv`, `waffe_elektronik_cpl.csv`. JLCPCB bestückt 73 Teile (Feld `LCSC`, Lagerbestand
geprüft, 11 Extended-Teile); die Stecker (BT1, SP1, J1, J2, J4–J6, J8, M1) und die Taster SW3/SW4
haben statt `LCSC` das Feld `LCSC Hand` und werden selbst gelötet. Mit allen Steckern und Tastern bestückt
(84 Teile, 19 Extended-Teile): `waffe_elektronik_bom_komplett.csv` + `waffe_elektronik_cpl_komplett.csv`, mit
externer Antenne `waffe_elektronik_bom_komplett_externe_antenne.csv` + `waffe_elektronik_cpl_komplett_externe_antenne.csv`.
Der SPI-NAND (U14 mit C25, R27) hat das Feld `LCSC Option` und steckt nur in den Varianten mit `_flash` am Ende
(+3 Teile, +1 Extended-Teil).
Selbst zu lötende Teile und lose Teile in der Waffe:
[`fertigung/lcsc/waffe_lose_teile.csv`](fertigung/lcsc/waffe_lose_teile.csv) (LCSC-Nummern, Menge je Waffe).
Alles für den Selbstbau bei Mouser: [`fertigung/mouser/`](fertigung/mouser/) (10 Waffen, Mouser-Vorlage) plus
[`lcsc_ergaenzung_10_waffen.csv`](fertigung/mouser/lcsc_ergaenzung_10_waffen.csv) für Teile, die Mouser nicht führt.

- Leiterplatte: 4 Lagen, 1,6 mm, Impedanz-Stackup JLC04161H-7628, ENIG, weißer Lötstopplack (Druck schwarz)
- Bestückung: Top Side, BOM + CPL hochladen, Platzierungsvorschau prüfen
- Teile: `U1` IP5306-I2C (ESOP-8, Extended), `D1`/`D4` B5819W (SOD-123, Basic), `D6` LBAT54CWT1G (SOT-323), `Q4` 2N7002 (Basic),
  `U16` TPS22810DBVR (SOT-23-6, Extended),
  22 µF CL21A226MAQNNNE (0805, Basic), `R7`/`R8` 22 Ω 1206 (Basic), `C3` TAJA106K016RNJ (Case A, Basic),
  `L1` 1 µH MWSA0503S-1R0MT

## Bekannte offene Punkte

- RMT-Kanal-Engpass bei 5 TSOPs (siehe
  [pinbelegung.md, Offene Fragen für den Praxistest](../../pinbelegung.md#offene-fragen-für-den-praxistest))
  ist hier nicht abgebildet, da rein softwareseitig
- Kein mechanischer Abgleich mit dem Waffengehäuse – Gehäusebasis siehe
  [../../gehaeuse/mp5_toygun_stls/](../../gehaeuse/mp5_toygun_stls/)

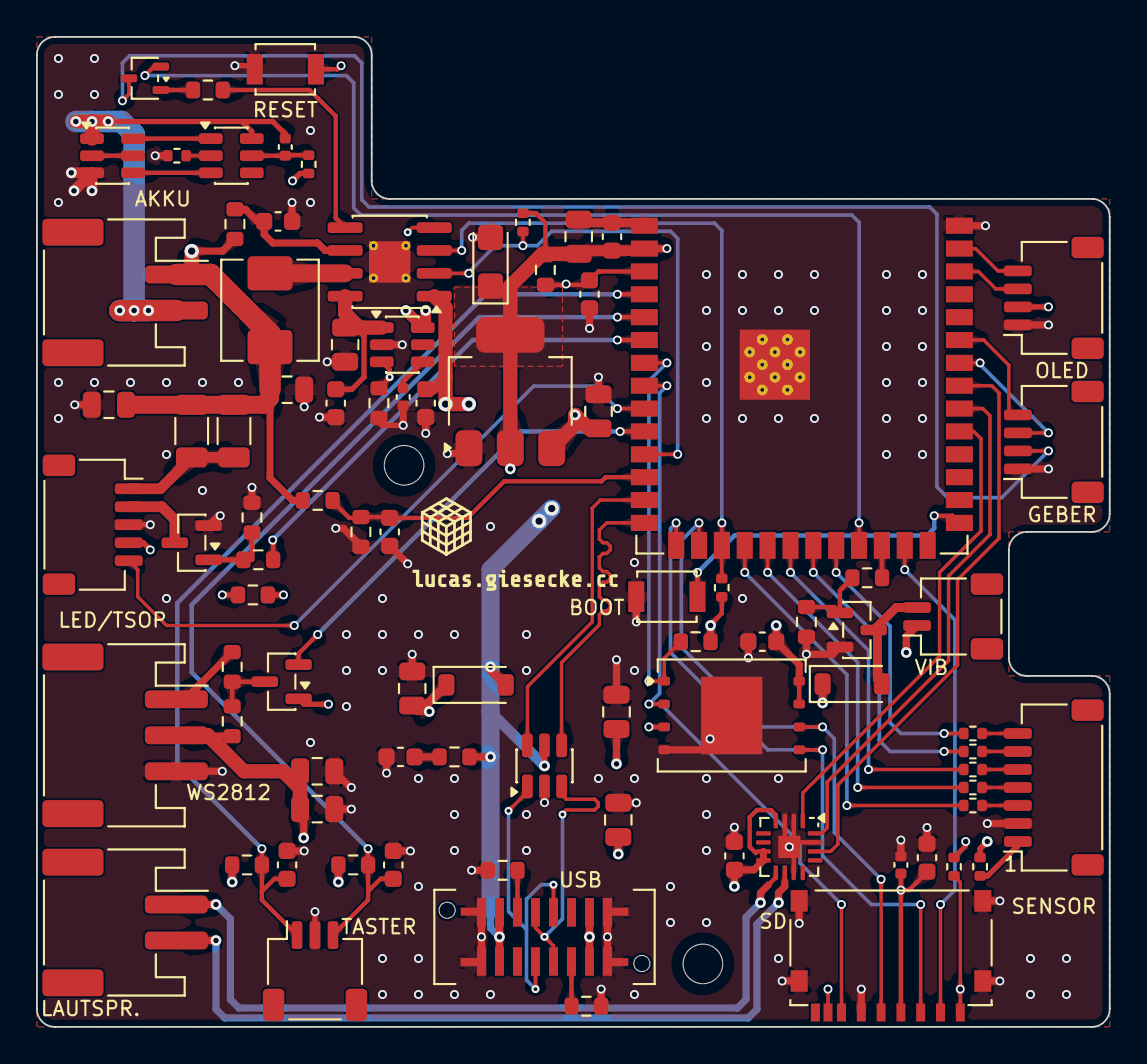
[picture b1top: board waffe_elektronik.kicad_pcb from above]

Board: 4 copper layers, 59.6 x 55.0 mm, 89 parts (0 on the bottom side), 72 nets.

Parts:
BT1: 1S LiPo 3,7 V; JST_PH_S2B-PH-SM4-TB_1x02-1MP_P2.00mm_Horizontal
C1, C7, C10, C19, C20, C31, C32: 22u; C_0805_2012Metric
C2, C18, C22: 10u; C_0805_2012Metric
C3: 10u; CP_EIA-3216-18_Kemet-A
C4, C28, C29, C30: 10u; C_0603_1608Metric
C5: 22u; C_0603_1608Metric
C6, C8, C9, C17, C23, C25: 100n; C_0603_1608Metric
C16: 1u; C_0603_1608Metric
C26, C27: 100n; C_0402_1005Metric
C33: 10n; C_0402_1005Metric
D1, D4: B5819W; D_SOD-123
D6: BAT54CW; SOT-323_SC-70
H1, H2: M2; MountingHole_2.2mm_M2_ISO7380
J1: WS2812 HP-Streifen; JST_PH_S3B-PH-SM4-TB_1x03-1MP_P2.00mm_Horizontal
J2: GX16 7-polig; JST_SH_SM07B-SRSS-TB_1x07-1MP_P1.00mm_Horizontal
J3: USB-C (Flashen + Laden); USB_C_Receptacle_HX_TYPE-C-16P-180-LT-H10.5_Vertical
J4: OLED I²C (Qwiic); JST_SH_SM04B-SRSS-TB_1x04-1MP_P1.00mm_Horizontal
J5: Drehgeber; JST_SH_SM04B-SRSS-TB_1x04-1MP_P1.00mm_Horizontal
J6: IR-LED + TSOP 6; JST_SH_SM05B-SRSS-TB_1x05-1MP_P1.00mm_Horizontal
J7: TF-018; microSD_TF-018_PushPull
J8: Abzug + Nachladen; JST_SH_SM03B-SRSS-TB_1x03-1MP_P1.00mm_Horizontal
L1: 1u; L_Sunlord_MWSA0503S
M1: Vibromotor; JST_SH_SM02B-SRSS-TB_1x02-1MP_P1.00mm_Horizontal
Q1, Q2: AO3400A; SOT-23
Q3: FS8205A; SOT-23-6
Q4: 2N7002; SOT-23
R1: 2; R_0603_1608Metric
R2: 1; R_0603_1608Metric
R3, R4: 1M; R_0603_1608Metric
R5, R11: 100; R_0603_1608Metric
R6, R12, R42: 100k; R_0603_1608Metric
R7, R8: 22; R_1206_3216Metric
R9, R10, R21, R24, R27: 10k; R_0603_1608Metric
R15: 330; R_0603_1608Metric
R22, R23: 5.1k; R_0603_1608Metric
R25: 1k; R_0603_1608Metric
R28, R30, R31, R32, R33, R34: 100; R_0402_1005Metric
R29: 1k; R_0402_1005Metric
R35: 10; R_0402_1005Metric
R36: 10; R_0603_1608Metric
R37: 10k; R_0402_1005Metric
R38, R40: 4.7k; R_0402_1005Metric
SP1: Lautsprecher; JST_PH_S2B-PH-SM4-TB_1x02-1MP_P2.00mm_Horizontal
SW3: RESET; SW_SPST_B3U-1000P
SW4: BOOT; SW_SPST_B3U-1000P
U1: IP5306-I2C; HSOP-8-1EP_3.9x4.9mm_P1.27mm_EP2.3x2.3mm_ThermalVias
U2: AMS1117-3.3; SOT-223-3_TabPin2
U4: ESP32-S3-WROOM-1-N16R8; ESP32-S3-WROOM-1
U6: MAX98357A; TQFN-16-1EP_3x3mm_P0.5mm_EP1.23x1.23mm
U12: USBLC6-2SC6; SOT-23-6
U14: ZD35Q1GC-IB; WSON-8-1EP_8x6mm_P1.27mm_EP3.4x4.3mm
U15: DW01A; SOT-23-6
U16: TPS22810; SOT-23-6

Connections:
3V3_J6: J6.4, R36.2
3V3_MCU: C3.1, C17.1, C18.1, C25.1, C26.1, C28.1, J4.2, J7.4, Q4.1, R9.1, R10.1, R21.1, R27.1, R35.1, R36.1, R37.2, R38.1, R40.1, U2.2, U4.2, U14.3, U14.7, U14.8
3V3_WESTE: J2.1, R35.2
5V_PERIPH: C1.1, C2.1, C10.1, C22.1, C23.1, C31.1, C32.1, D1.1, D4.1, J1.2, M1.1, R25.1, U2.3, U6.4, U6.7, U6.8, U16.6
ADC_BATT: C6.1, R3.2, R4.1, U4.12
BAT_N: BT1.2, C27.2, Q3.1, U15.6
BAT_P: BT1.1, C7.1, C19.1, L1.2, R2.2, R3.1, R7.1, R8.1, R28.1
ENC_A: J5.4, U4.35
ENC_B: J5.3, U4.34
ENC_SW: D6.2, U4.23
FLASH_CS: R27.2, U4.7, U14.1
GND: C1.2, C2.2, C3.2, C4.2, C5.2, C6.2, C7.2, C8.2, C9.2, C10.2, C16.2, C17.2, C18.2, C19.2, C20.2, C22.2, C23.2, C25.2, C26.2, C28.2, C29.2, C30.2, C31.2, C32.2, C33.2, J1.3, J2.2, J3.A1, J3.A12, J3.B1, J3.B12, J3.SH, J4.1, J5.1, J6.3, J7.6, J7.SH, J8.2, Q1.2, Q2.2, Q3.3, R4.2, R6.2, R12.2, R22.2, R23.2, R29.2, R42.2, SW3.1, SW4.1, U1.9, U2.1, U4.1, U4.40, U4.41, U6.2, U6.3, U6.11, U6.15, U6.17, U12.2, U14.4, U14.9, U16.2
I2C_SCL: J4.4, U4.39
I2C_SDA: J4.3, U4.38
I2S_BCLK: U4.32, U6.16
I2S_DOUT: U4.31, U6.1
I2S_LRCLK: U4.33, U6.14
IP_IRQ: R42.1, U1.4, U16.3
IP_KEY: R24.1, U1.5
IP_SCL: R40.2, U1.2, U4.11
IP_SDA: R38.2, U1.3, U4.17
IR_GATE: R5.1, U4.6
IR_LED_A: J6.1, R7.2, R8.2
IR_LED_K: J6.2, Q1.3
unnamed: C29.1, R1.2
unnamed: D1.2, M1.2, Q2.3
unnamed: D6.1, R24.2
unnamed: J1.1, R15.2
unnamed: J3.A5, R23.1
unnamed: J3.B5, R22.1
unnamed: J3.A6, J3.B6, U12.3
unnamed: J3.A7, J3.B7, U12.1
unnamed: Q1.1, R5.2, R6.1
unnamed: Q2.1, R11.2, R12.1
unnamed: Q3.2, Q3.5
unnamed: Q3.6, U15.1
unnamed: Q3.4, U15.3
unnamed: Q4.3, R15.1, R25.2
unnamed: C5.1, R2.1, U1.6
unnamed: L1.1, U1.7
unnamed: C20.1, C30.1, U1.8, U16.1
unnamed: C16.1, R21.2, SW3.2, U4.3
unnamed: SW4.2, U4.27
unnamed: SP1.2, U6.10
unnamed: SP1.1, U6.9
unnamed: R29.1, U15.2
unnamed: C27.1, R28.2, U15.5
unnamed: C33.1, U16.4
PWR_KEY: D6.3, J5.2
RELOAD: C9.1, J8.3, R10.2, U4.5
SD_CS: J7.2, U4.25
SD_DAT12: J7.1, J7.8, R37.1
SPI_CLK: J7.5, U4.16, U14.6
SPI_MISO: J7.7, U4.8, U14.2
SPI_MOSI: J7.3, U4.15, U14.5
TRIGGER: C8.1, J8.1, R9.2, U4.4
TSOP1_J: J2.3, R30.2
TSOP1_OUT: R30.1, U4.18
TSOP2_J: J2.4, R31.2
TSOP2_OUT: R31.1, U4.19
TSOP3_J: J2.5, R32.2
TSOP3_OUT: R32.1, U4.20
TSOP4_J: J2.6, R33.2
TSOP4_OUT: R33.1, U4.21
TSOP5_J: J2.7, R34.2
TSOP5_OUT: R34.1, U4.22
TSOP6_OUT: J6.5, U4.9
USB_D+: U4.14, U12.4
USB_D-: U4.13, U12.6
VBUS_NATIVE: C4.1, D4.2, J3.A4, J3.A9, J3.B4, J3.B9, R1.1, U1.1, U12.5
VIB: R11.1, U4.24
WS2812_DIN_3V3: Q4.2, U4.10

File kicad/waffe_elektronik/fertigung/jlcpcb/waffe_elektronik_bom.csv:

Comment,Designator,Footprint,LCSC Part #
22u,"C1,C7,C10,C19,C20,C31,C32",C_0805_2012Metric,C45783
10u,"C2,C18,C22",C_0805_2012Metric,C15850
10u,C3,CP_EIA-3216-18_Kemet-A,C7171
10u,"C4,C28,C29,C30",C_0603_1608Metric,C19702
22u,C5,C_0603_1608Metric,C59461
100n,"C6,C8,C9,C17,C23",C_0603_1608Metric,C14663
1u,C16,C_0603_1608Metric,C15849
100n,"C26,C27",C_0402_1005Metric,C1525
10n,C33,C_0402_1005Metric,C15195
B5819W,"D1,D4",D_SOD-123,C8598
BAT54CW,D6,SOT-323_SC-70,C57891
USB-C (Flashen + Laden),J3,USB_C_Receptacle_HX_TYPE-C-16P-180-LT-H10.5_Vertical,C49261570
TF-018,J7,microSD_TF-018_PushPull,C961679
1u,L1,L_Sunlord_MWSA0503S,C408355
AO3400A,"Q1,Q2",SOT-23,C20917
FS8205A,Q3,SOT-23-6,C2830320
2N7002,Q4,SOT-23,C8545
2,R1,R_0603_1608Metric,C22977
1,R2,R_0603_1608Metric,C22936
1M,"R3,R4",R_0603_1608Metric,C22935
100,"R5,R11",R_0603_1608Metric,C22775
100k,"R6,R12,R42",R_0603_1608Metric,C25803
22,"R7,R8",R_1206_3216Metric,C17958
10k,"R9,R10,R21,R24",R_0603_1608Metric,C25804
330,R15,R_0603_1608Metric,C23138
5.1k,"R22,R23",R_0603_1608Metric,C23186
1k,R25,R_0603_1608Metric,C21190
100,"R28,R30,R31,R32,R33,R34",R_0402_1005Metric,C25076
1k,R29,R_0402_1005Metric,C11702
10,R35,R_0402_1005Metric,C25077
10,R36,R_0603_1608Metric,C22859
10k,R37,R_0402_1005Metric,C25744
4.7k,"R38,R40",R_0402_1005Metric,C25900
IP5306-I2C,U1,HSOP-8-1EP_3.9x4.9mm_P1.27mm_EP2.3x2.3mm_ThermalVias,C488349
AMS1117-3.3,U2,SOT-223-3_TabPin2,C6186
ESP32-S3-WROOM-1-N16R8,U4,ESP32-S3-WROOM-1,C2913202
MAX98357A,U6,TQFN-16-1EP_3x3mm_P0.5mm_EP1.23x1.23mm,C910544
USBLC6-2SC6,U12,SOT-23-6,C7519
DW01A,U15,SOT-23-6,C351410
TPS22810,U16,SOT-23-6,C205990

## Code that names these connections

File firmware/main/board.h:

// Pin assignment of the weapon board, see pinbelegung.md and
// kicad/waffe_elektronik (netlist U4).
#pragma once

#include "driver/gpio.h"

#define PIN_TRIGGER     GPIO_NUM_4   // active low, 10k pull-up + 100n
#define PIN_RELOAD      GPIO_NUM_5   // active low, 10k pull-up + 100n
#define PIN_IR_GATE     GPIO_NUM_6   // AO3400 gate, high = IR LED on
#define PIN_BAT_ADC     GPIO_NUM_8   // ADC1_CH7, 1M/1M divider straight from the cell (BAT_P)
#define PIN_WS2812      GPIO_NUM_17  // via 74HCT125 to the strip
#define PIN_I2S_DOUT    GPIO_NUM_38
#define PIN_I2S_BCLK    GPIO_NUM_39
#define PIN_I2S_LRCLK   GPIO_NUM_40
#define PIN_VIB         GPIO_NUM_47  // AO3400 gate, one motor for recoil and hit

// Operator panel: OLED on I2C (J4, Qwiic pinout, pull-ups on the display
// module) and rotary encoder with push button (J5, contacts to GND, use the
// internal pull-ups). Not used by the firmware yet.
#define PIN_I2C_SCL     GPIO_NUM_1
#define PIN_I2C_SDA     GPIO_NUM_2
#define PIN_ENC_A       GPIO_NUM_42
#define PIN_ENC_B       GPIO_NUM_41
#define PIN_ENC_SW      GPIO_NUM_21  // also switches the board on (IP5306 KEY through D6)

// IP5306-I2C charger + 5 V boost (U1) on its own I2C bus, 4.7k pull-ups
#define PIN_IP5306_SCL  GPIO_NUM_18
#define PIN_IP5306_SDA  GPIO_NUM_9
#define IP5306_ADDR     0x75

// TSOP34838 outputs, idle high, low while a 38 kHz burst is received.
// Index = sensor number - 1.
#define PIN_TSOP1       GPIO_NUM_10  // headband front
#define PIN_TSOP2       GPIO_NUM_11  // headband back
#define PIN_TSOP3       GPIO_NUM_12  // chest
#define PIN_TSOP4       GPIO_NUM_13  // back
#define PIN_TSOP5       GPIO_NUM_14  // shoulders (optional)
#define PIN_TSOP6       GPIO_NUM_16  // on the weapon itself, connector J6

#define BAT_DIVIDER     2            // BAT_P = 2 * ADC voltage
#define BAT_ADC_UNIT    ADC_UNIT_1
#define BAT_ADC_CHANNEL ADC_CHANNEL_7
